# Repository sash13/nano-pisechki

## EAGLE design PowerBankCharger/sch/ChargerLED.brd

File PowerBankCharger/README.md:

PCB for PowerBank charger
==========
This pcb for:
- Start\Stop charge
- Control Voltage on accumulator
- Inform charger level

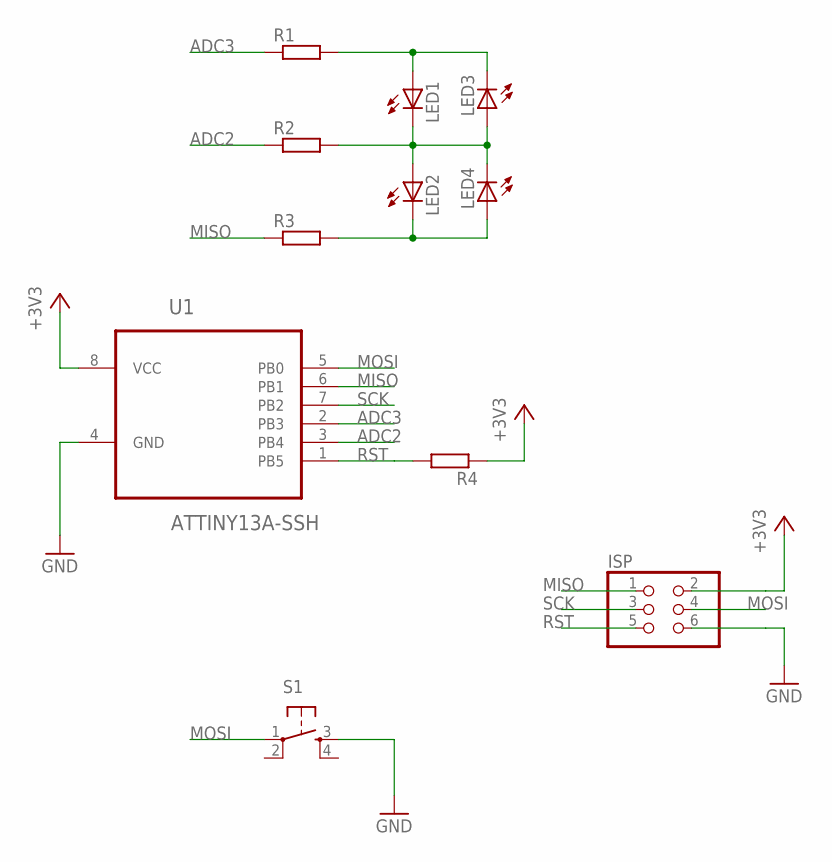
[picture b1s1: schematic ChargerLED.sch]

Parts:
ISP: PINHD-2X3; 2X03
LED1, LED2, LED3, LED4: LEDCHIP-LED0603; CHIP-LED0603
R1, R2, R3, R4: R-EU_R0603; R0603
S1: TAC_SWITCHSMD; TACTILE_SWITCH_SMD
U1: ATTINY13A-SSH; SOIC127P600X175-8N

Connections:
+3V3: ISP.2, R4.1, U1.8 (VCC)
ADC2: R2.1, U1.3 (PB4)
ADC3: R1.1, U1.2 (PB3)
GND: ISP.6, S1.3, U1.4 (GND)
MISO: ISP.1, R3.1, U1.6 (PB1)
MOSI: ISP.4, S1.1, U1.5 (PB0)
unnamed: LED1.C, LED2.A, LED3.A, LED4.C, R2.2
unnamed: LED2.C, LED4.A, R3.2
unnamed: LED1.A, LED3.C, R1.2
RST: ISP.5, R4.2, U1.1 (PB5)
SCK: ISP.3, U1.7 (PB2)

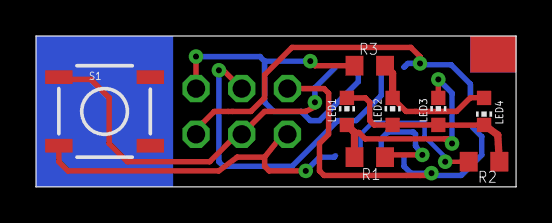
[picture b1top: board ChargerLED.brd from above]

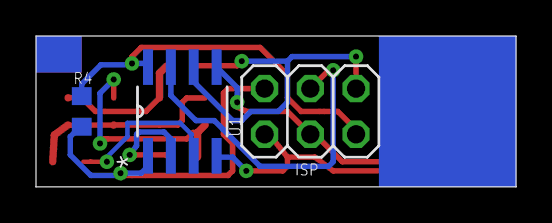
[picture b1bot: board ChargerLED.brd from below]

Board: 2 copper layers, 26.7 x 8.4 mm, 11 parts (3 on the bottom side), 11 nets.

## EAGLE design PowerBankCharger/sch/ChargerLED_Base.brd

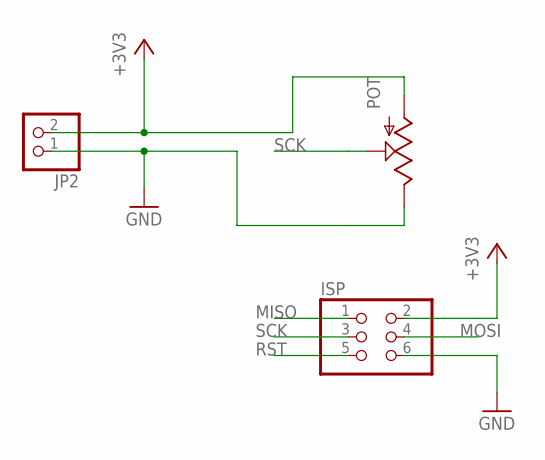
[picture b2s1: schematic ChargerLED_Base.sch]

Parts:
ISP: PINHD-2X3; 2X03
JP2: PINHD-1X2/90; 1X02/90
POT: POT-RV16AF-20; POT_ALPHA_RV16AF-20

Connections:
+3V3: ISP.2, JP2.2, POT.1 (A)
GND: ISP.6, JP2.1, POT.3 (E)
MISO: ISP.1
MOSI: ISP.4
RST: ISP.5
SCK: ISP.3, POT.2 (S)

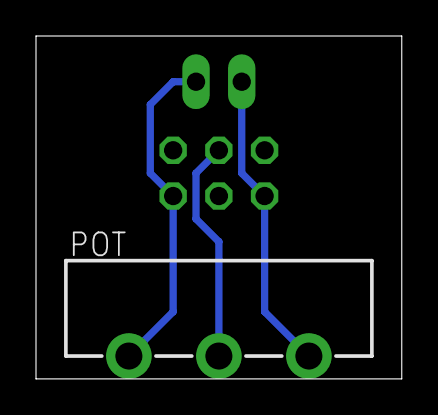
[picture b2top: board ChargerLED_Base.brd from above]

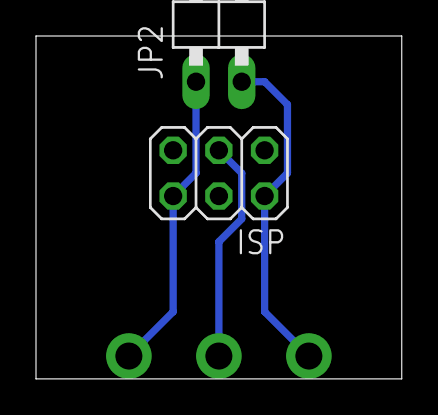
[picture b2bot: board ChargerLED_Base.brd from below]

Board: 2 copper layers, 20.3 x 19.1 mm, 3 parts (2 on the bottom side), 3 nets.

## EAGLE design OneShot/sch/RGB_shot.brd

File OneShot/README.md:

One shot
==========
RGB led project.
One button with multitapping feature for many type of event.

Based on attiny13 controller

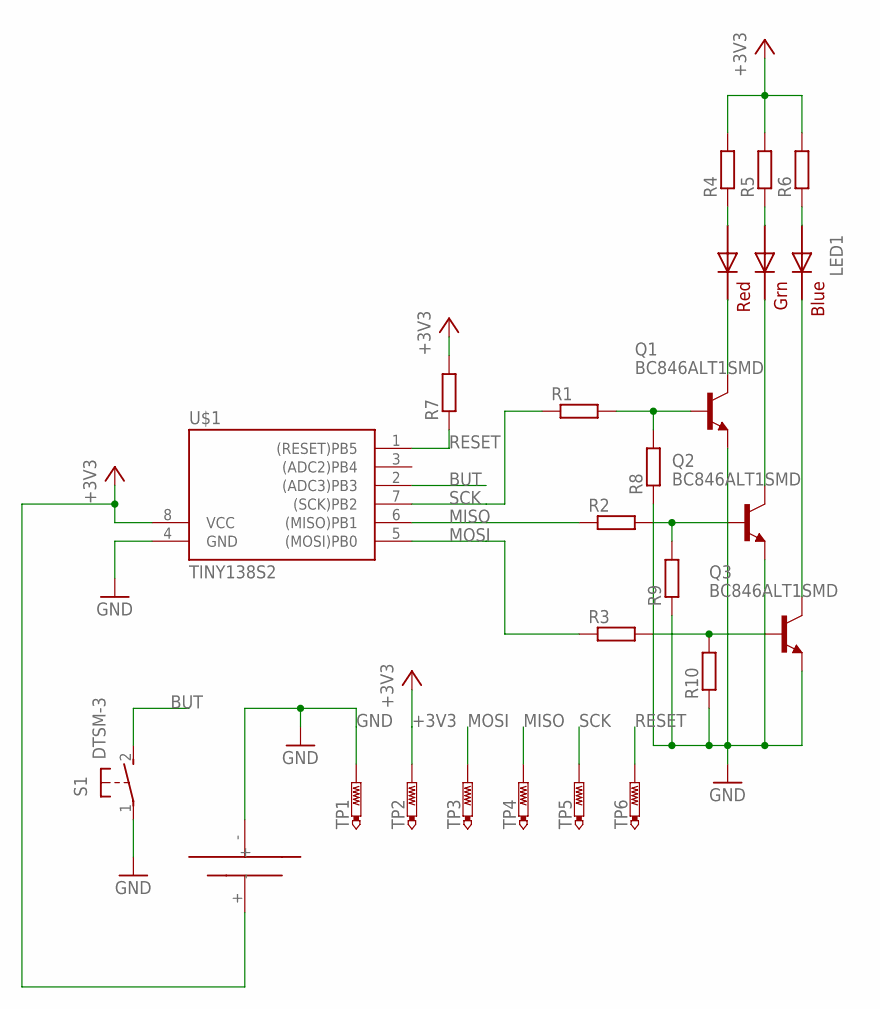
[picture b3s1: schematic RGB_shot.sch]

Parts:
LED1: RGBLED5050
Q1, Q2, Q3: BC846ALT1SMD; SOT23
R1, R2, R3, R4, R5, R6, R7, R8, R9, R10: R-EU_M0805; M0805
S1: DTSM-3
TP1, TP2, TP3, TP4, TP5, TP6: PTR1TP11R; TP11R
U$1: TINY138S2; SO08
U$2: BAT33_1220; BAT1220

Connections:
+3V3: R4.2, R5.2, R6.2, R7.2, TP2.TP, U$1.8 (VCC), U$2.+
BUT: S1.2, U$1.2 ((ADC3)PB3)
GND: Q1.2 (E), Q2.2 (E), Q3.2 (E), R8.1, R9.1, R10.1, S1.1, TP1.TP, U$1.4 (GND), U$2.-
MISO: R2.1, TP4.TP, U$1.6 ((MISO)PB1)
MOSI: R3.1, TP3.TP, U$1.5 ((MOSI)PB0)
unnamed: LED1.2 (RED_A), R4.1
unnamed: LED1.1 (GREEN_A), R5.1
unnamed: LED1.3 (BLUE_A), R6.1
unnamed: LED1.5 (RED_C), Q1.3 (C)
unnamed: LED1.6 (GREEN_C), Q2.3 (C)
unnamed: LED1.4 (BLUE_C), Q3.3 (C)
unnamed: Q1.1 (B), R1.2, R8.2
unnamed: Q2.1 (B), R2.2, R9.2
unnamed: Q3.1 (B), R3.2, R10.2
RESET: R7.1, TP6.TP, U$1.1 ((RESET)PB5)
SCK: R1.1, TP5.TP, U$1.7 ((SCK)PB2)

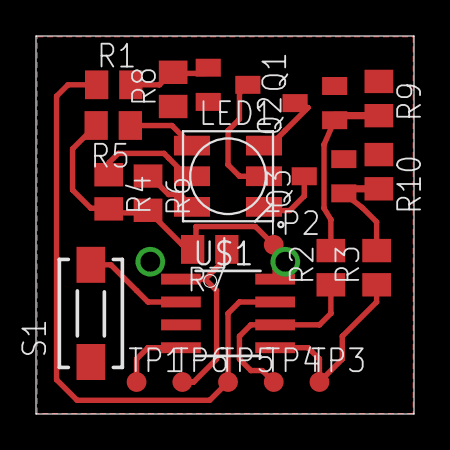
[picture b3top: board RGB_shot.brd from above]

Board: 2 copper layers, 21.0 x 21.0 mm, 23 parts (0 on the bottom side), 16 nets.

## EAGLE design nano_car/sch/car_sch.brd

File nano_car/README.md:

Nano car
==========
Micro car controlling by IR remoute.

Based on attiny10 controller

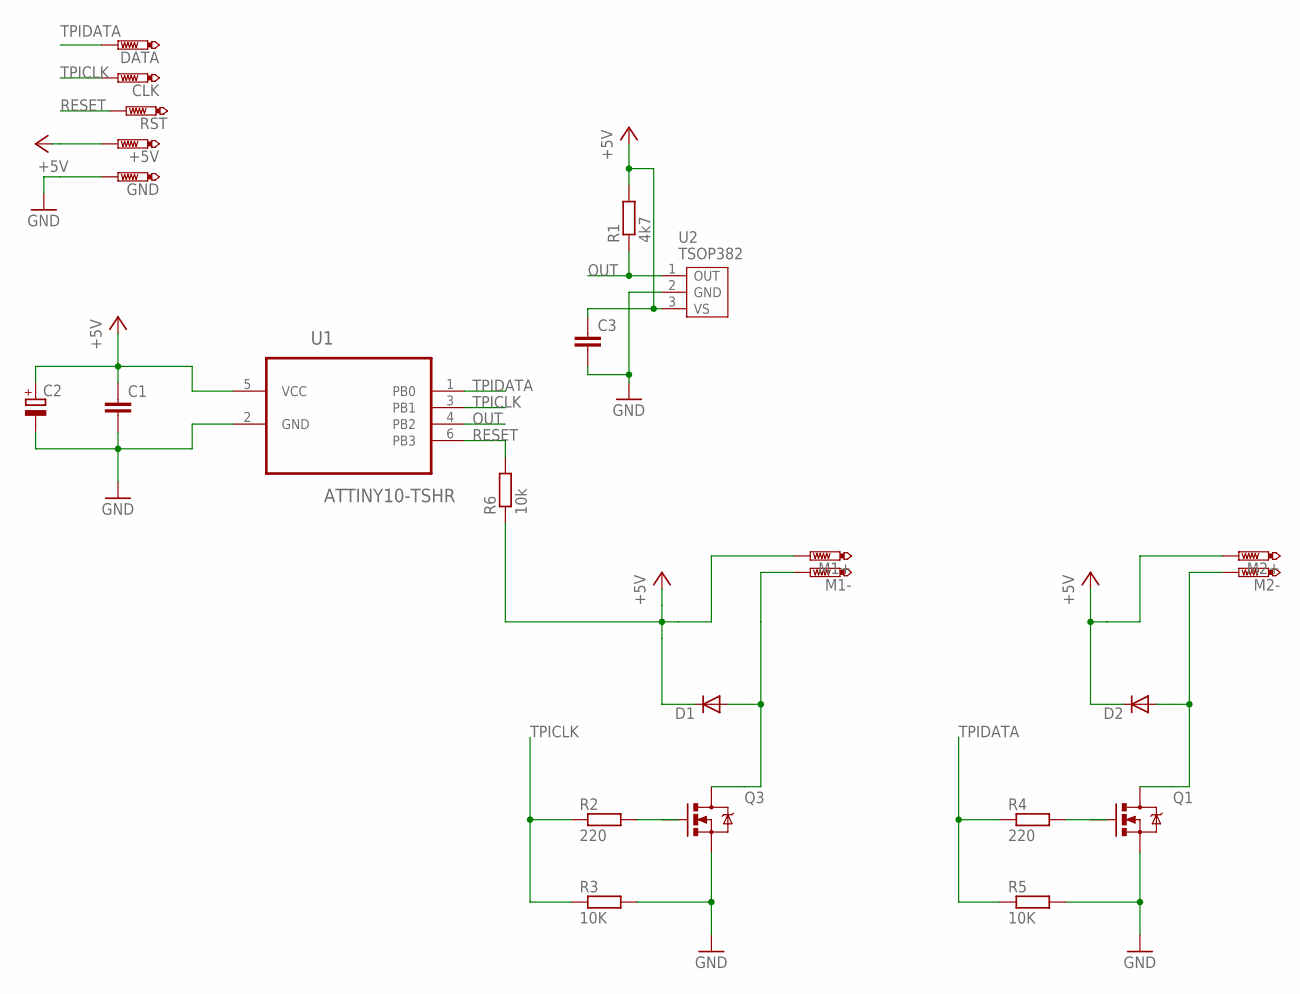
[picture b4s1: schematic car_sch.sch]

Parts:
+5V: PTR1TP11R; TP11R
C1, C3: C-EUC0603; C0603
C2: CPOL-EUSMCA; SMC_A
CLK: PTR1TP11R; TP11R
D1, D2: DIODESOD; SOD-323
DATA: PTR1TP11R; TP11R
GND: PTR1TP11R; TP11R
M1+, M1-, M2+, M2-: PTR1TP11R; TP11R
Q1, Q3: MOSFET-NCHANNELBSS123LT1G; SOT23
R1: 4k7; R0603
R2, R4: 220; R0603
R3, R5: 10K; R0603
R6: 10k; R0603
RST: PTR1TP11R; TP11R
U1: ATTINY10-TSHR; SOT95P280X145-6N
U2: TSOP382; 3P-2.54-4.8X5X6.95H

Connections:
+5V: +5V.TP, C1.1, C2.+, C3.1, D1.1 (C), D2.1 (C), M1+.TP, M2+.TP, R1.2, R6.1, U1.5 (VCC), U2.3 (VS)
GND: C1.2, C2.-, C3.2, GND.TP, Q1.2 (S), Q3.2 (S), R3.2, R5.2, U1.2 (GND), U2.2 (GND)
unnamed: Q1.1 (G), R4.2
unnamed: D2.2 (A), M2-.TP, Q1.3 (D)
unnamed: Q3.1 (G), R2.2
unnamed: D1.2 (A), M1-.TP, Q3.3 (D)
OUT: R1.1, U1.4 (PB2), U2.1 (OUT)
RESET: R6.2, RST.TP, U1.6 (PB3)
TPICLK: CLK.TP, R2.1, R3.1, U1.3 (PB1)
TPIDATA: DATA.TP, R4.1, R5.1, U1.1 (PB0)

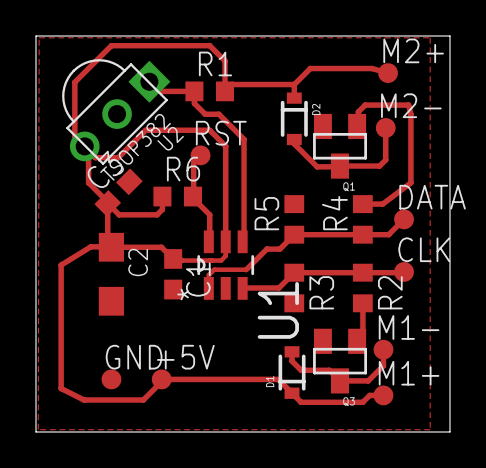
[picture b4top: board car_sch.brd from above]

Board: 2 copper layers, 23.0 x 22.0 mm, 24 parts (0 on the bottom side), 10 nets.

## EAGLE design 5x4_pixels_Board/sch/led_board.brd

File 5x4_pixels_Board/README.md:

Mini led Matrix 5x4
==========
Mini circled board 0.80x0.80 inch (20.35x20.35 mm) size

[Youtube presentation][1]

Based on attiny13 controller

[1]: https://www.youtube.com/watch?v=8r0_19418MQ

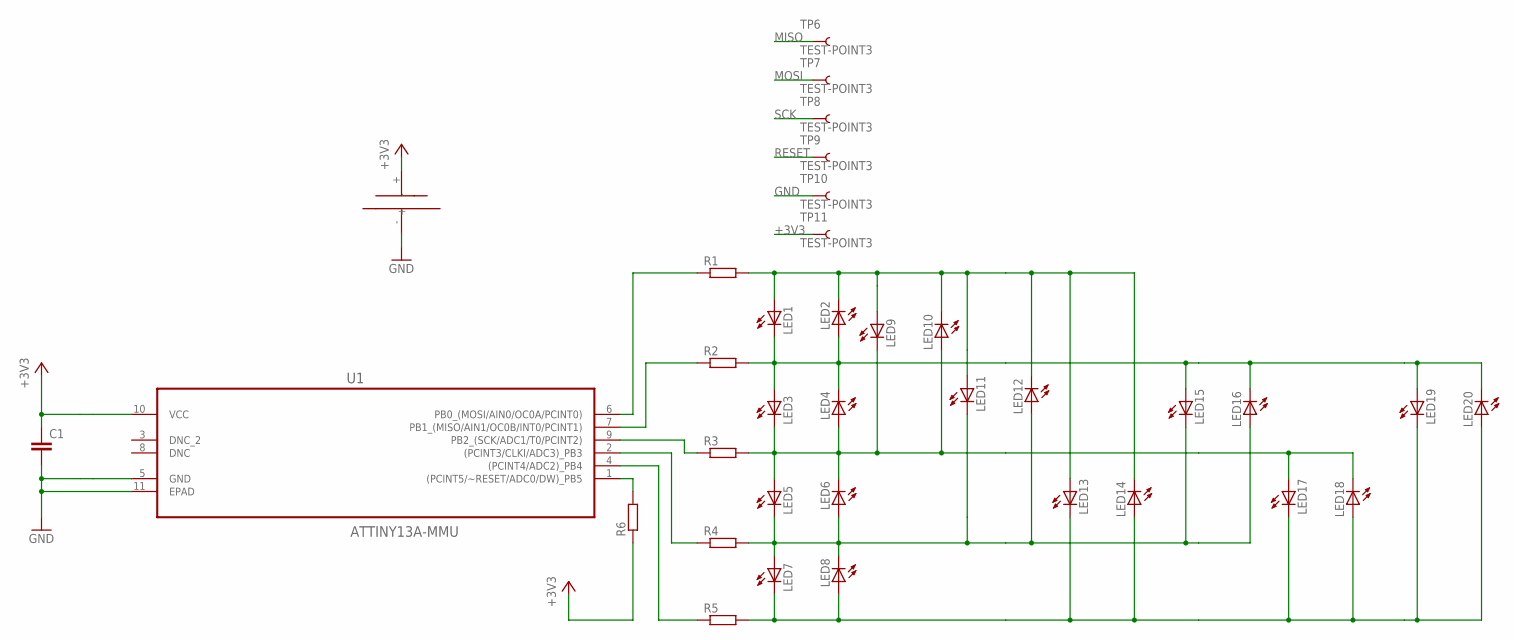
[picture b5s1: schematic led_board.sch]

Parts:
C1: C-EUC0603; C0603
LED1, LED2, LED3, LED4, LED5, LED6, LED7, LED8, LED9, LED10, LED11, LED12, LED13, LED14, LED15, LED16, LED17, LED18, LED19, LED20: LED0603; LED-0603
R1, R2, R3, R4, R5, R6: R-EU_R0603; R0603
TP6, TP7, TP8, TP9, TP10, TP11: TEST-POINT3; PAD.03X.03
U1: ATTINY13A-MMU; DFN300X300X100-11N
U$1: BH500; BAT1220_BH500

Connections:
+3V3: C1.1, R6.1, TP11.P$1, U1.10 (VCC), U$1.+
GND: C1.2, TP10.P$1, U1.5 (GND), U1.11 (EPAD), U$1.-
MISO: R2.1, TP6.P$1, U1.7 (PB1_(MISO/AIN1/OC0B/INT0/PCINT1))
MOSI: R1.1, TP7.P$1, U1.6 (PB0_(MOSI/AIN0/OC0A/PCINT0))
unnamed: LED5.C, LED6.A, LED7.A, LED8.C, LED11.C, LED12.A, LED15.C, LED16.A, R4.2
unnamed: LED1.C, LED2.A, LED3.A, LED4.C, LED15.A, LED16.C, LED19.A, LED20.C, R2.2
unnamed: LED3.C, LED4.A, LED5.A, LED6.C, LED9.C, LED10.A, LED17.A, LED18.C, R3.2
unnamed: LED7.C, LED8.A, LED13.C, LED14.A, LED17.C, LED18.A, LED19.C, LED20.A, R5.2
unnamed: LED1.A, LED2.C, LED9.A, LED10.C, LED11.A, LED12.C, LED13.A, LED14.C, R1.2
unnamed: R4.1, U1.2 ((PCINT3/CLKI/ADC3)_PB3)
unnamed: R5.1, U1.4 ((PCINT4/ADC2)_PB4)
RESET: R6.2, TP9.P$1, U1.1 ((PCINT5/~RESET/ADC0/DW)_PB5)
SCK: R3.1, TP8.P$1, U1.9 (PB2_(SCK/ADC1/T0/PCINT2))

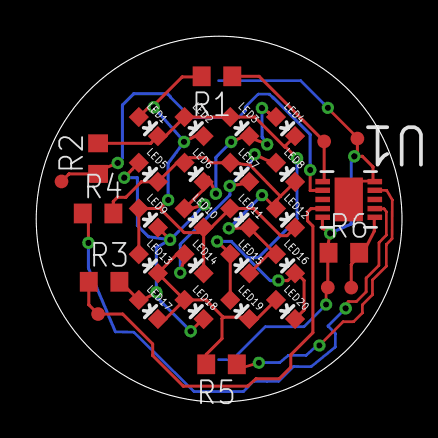
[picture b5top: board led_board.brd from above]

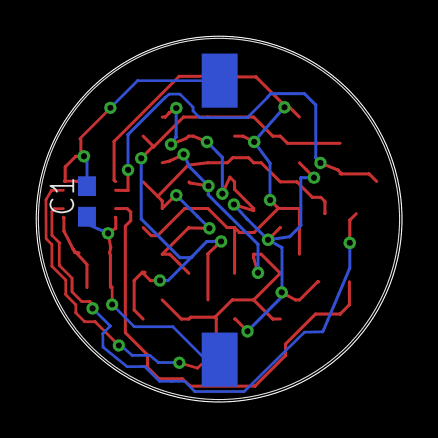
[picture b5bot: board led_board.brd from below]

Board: 2 copper layers, 20.3 x 20.3 mm, 35 parts (2 on the bottom side), 13 nets.

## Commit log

2015-03-22 Add eagle schematics for matrix led
2015-03-22 Correct index
2015-03-22 Ignore eagle project file
2015-03-22 Add programm files
2015-03-22 Correct chars print in matrix
2015-04-03 New projects
    Nano car and one button one led
2015-04-03 Fix wire spacing
    More spacing between wire for freely laser-iron production
2015-04-03 Add programm file for oneShot
2015-04-11 Fix message showen
2015-04-13 Add some defines
2015-04-13 Resize image in readme
2015-04-14 Test new sleep mode for power consumption
2015-04-17 Minor fix and space handler in message
2015-04-18 Power mode delete
2015-04-18 Add missing symbols
2016-05-28 Add pcb for Charger
2016-05-28 Add readme to powerbank

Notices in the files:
parts and their libraries:
SparkFun-LED: Licensing: CC v3.0 Share-Alike You are welcome to use this library for commercial purposes.
